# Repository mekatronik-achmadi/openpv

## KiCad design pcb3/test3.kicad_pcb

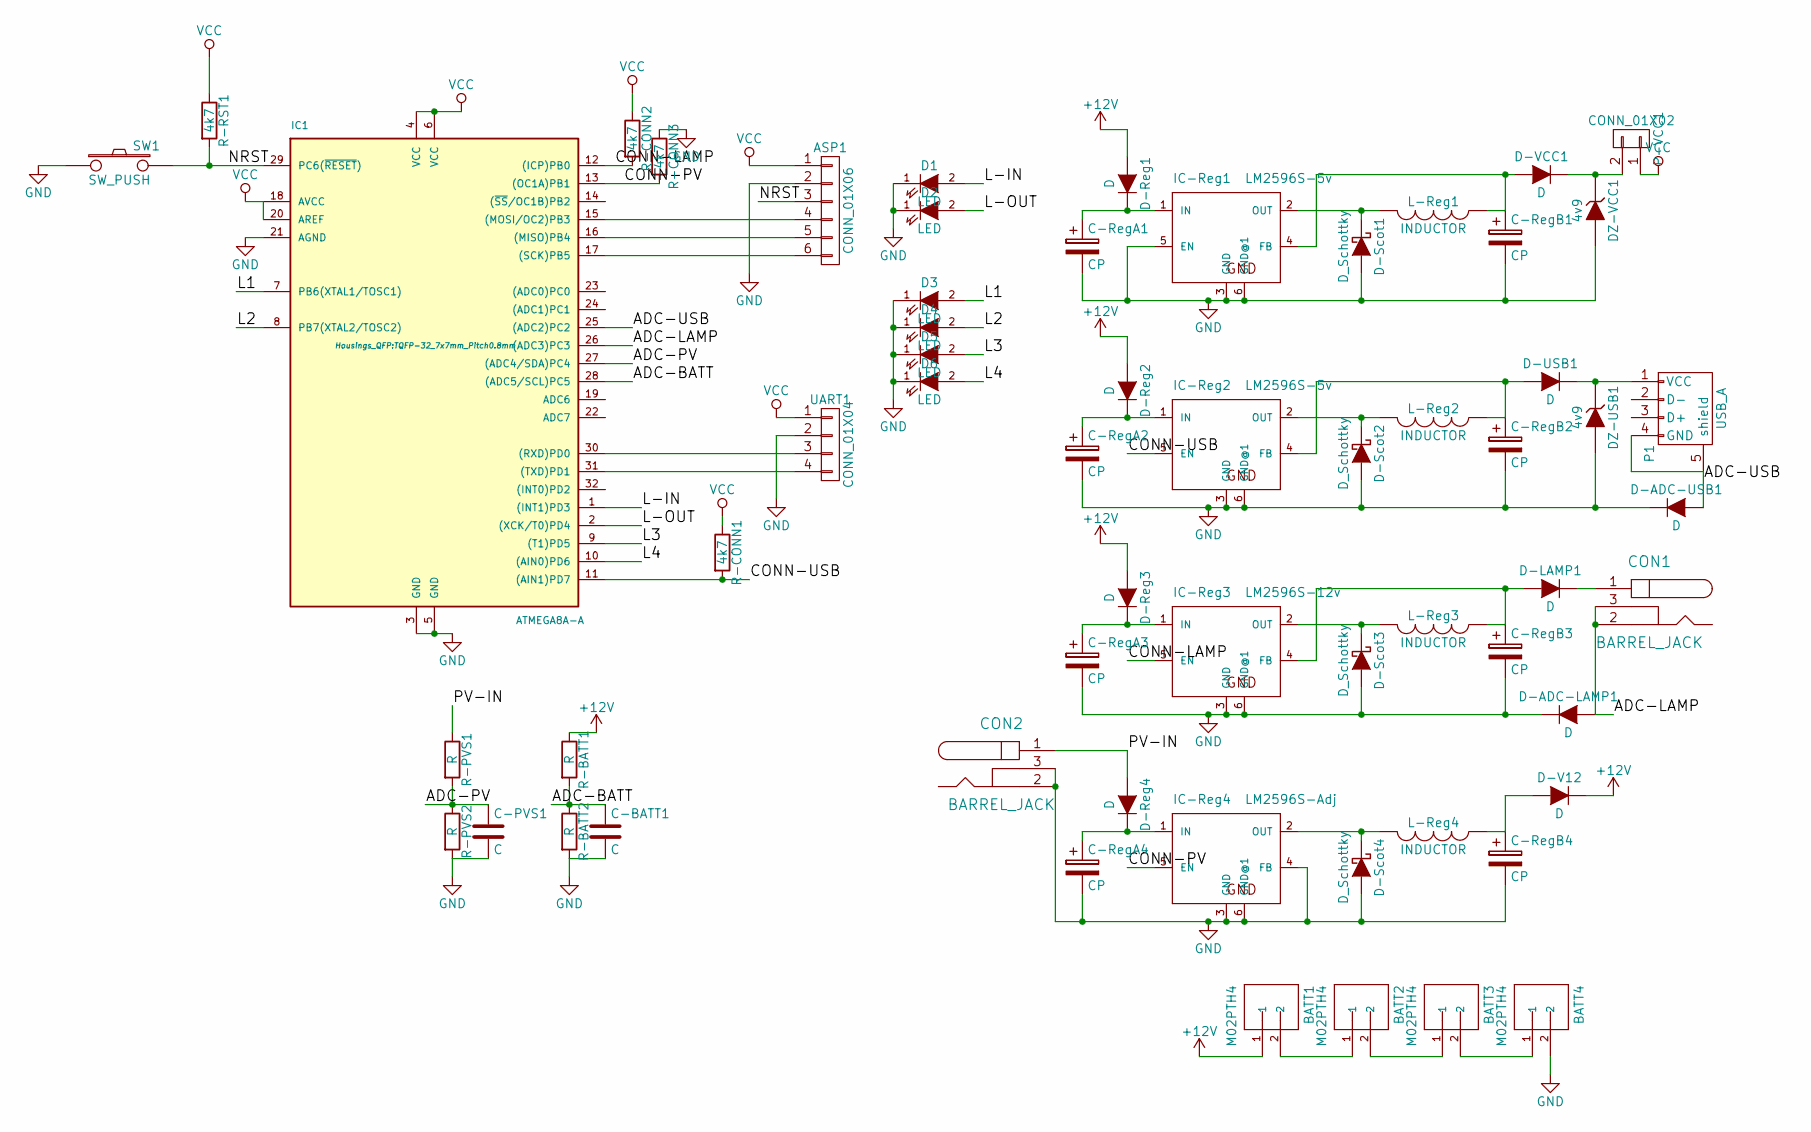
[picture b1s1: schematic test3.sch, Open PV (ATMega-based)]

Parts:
ASP1: CONN_01X06; Pin_Header_Straight_1x06
BATT1, BATT2, BATT3, BATT4: M02PTH4; SparkFun-1X02_XTRA_BIG
C-BATT1: C; C_Rect_L7_W2_P5
C-PVS1: C; C_Rect_L7_W2_P5
C-RegA1, C-RegA2, C-RegA3, C-RegA4: CP; C_Radial_D5_L6_P2.5
C-RegB1, C-RegB2, C-RegB3, C-RegB4: CP; C_Radial_D5_L6_P2.5
CON1, CON2: BARREL_JACK; JACK_ALIM
D1, D2, D3, D4, D5, D6: LED; LED-3MM
D-ADC-LAMP1: D; Diode_DO-35_SOD27_Horizontal_RM10
D-ADC-USB1: D; Diode_DO-35_SOD27_Horizontal_RM10
D-LAMP1: D; Diode_DO-35_SOD27_Horizontal_RM10
D-Reg1, D-Reg2, D-Reg3, D-Reg4: D; Diode_DO-35_SOD27_Horizontal_RM10
D-Scot1, D-Scot2, D-Scot3, D-Scot4: D_Schottky; Diode_DO-35_SOD27_Horizontal_RM10
D-USB1: D; Diode_DO-35_SOD27_Horizontal_RM10
D-V12: D; Diode_DO-35_SOD27_Horizontal_RM10
D-VCC1: D; Diode_DO-35_SOD27_Horizontal_RM10
DZ-USB1: 4v9; Diode_DO-35_SOD27_Horizontal_RM10
DZ-VCC1: 4v9; Diode_DO-35_SOD27_Horizontal_RM10
IC1: ATMEGA8A-A; TQFP-32_7x7mm_Pitch0.8mm
IC-Reg1, IC-Reg2: LM2596S-5v; TO-263-5Lead
IC-Reg3: LM2596S-12v; TO-263-5Lead
IC-Reg4: LM2596S-Adj; TO-263-5Lead
L-Reg1, L-Reg2, L-Reg3, L-Reg4: INDUCTOR; INDUCTOR_V
P1: USB_A
P-VCC1: CONN_01X02; Pin_Header_Straight_1x02
R-BATT1, R-BATT2: R; Resistor_Horizontal_RM10mm
R-CONN1, R-CONN2, R-CONN3: 4k7; Resistor_Horizontal_RM10mm
R-PVS1, R-PVS2: R; Resistor_Horizontal_RM10mm
R-RST1: 4k7; Resistor_Horizontal_RM10mm
SW1: SW_PUSH; switch-omron-B3F-10XX
UART1: CONN_01X04; Pin_Header_Straight_1x04

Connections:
+12V: BATT1.1, D-Reg1.2 (A), D-Reg2.2 (A), D-Reg3.2 (A), D-V12.1 (K), R-BATT1.1
/ADC-BATT: C-BATT1.1, IC1.28 ((ADC5/SCL)PC5), R-BATT1.2, R-BATT2.1
/ADC-LAMP: CON1.2, CON1.3, D-ADC-LAMP1.2 (A), IC1.26 ((ADC3)PC3)
/ADC-PV: C-PVS1.1, IC1.27 ((ADC4/SDA)PC4), R-PVS1.2, R-PVS2.1
/ADC-USB: D-ADC-USB1.2 (A), IC1.25 ((ADC2)PC2), P1.4 (GND), P1.5 (shield)
/CONN-LAMP: IC1.12 ((ICP)PB0), IC-Reg3.5 (EN), R-CONN2.2
/CONN-PV: IC1.13 ((OC1A)PB1), IC-Reg4.5 (EN), R-CONN3.2
/CONN-USB: IC1.11 ((AIN1)PD7), IC-Reg2.5 (EN), R-CONN1.2
/L1: D3.2 (A), IC1.7 (PB6(XTAL1/TOSC1))
/L2: D4.2 (A), IC1.8 (PB7(XTAL2/TOSC2))
/L3: D5.2 (A), IC1.9 ((T1)PD5)
/L4: D6.2 (A), IC1.10 ((AIN0)PD6)
/L-IN: D1.2 (A), IC1.1 ((INT1)PD3)
/L-OUT: D2.2 (A), IC1.2 ((XCK/T0)PD4)
/NRST: ASP1.3, IC1.29 (PC6(~RESET~)), R-RST1.2, SW1.2
/PV-IN: CON2.1, D-Reg4.2 (A), R-PVS1.1
GND: ASP1.2, BATT4.2, C-BATT1.2, C-PVS1.2, C-RegA1.2, C-RegA2.2, C-RegA3.2, C-RegA4.2, C-RegB1.2, C-RegB2.2, C-RegB3.2, C-RegB4.2, CON2.2, CON2.3, D1.1 (K), D2.1 (K), D3.1 (K), D4.1 (K), D5.1 (K), D6.1 (K), D-ADC-LAMP1.1 (K), D-ADC-USB1.1 (K), D-Scot1.2 (A), D-Scot2.2 (A), D-Scot3.2 (A), D-Scot4.2 (A), DZ-USB1.2 (A), DZ-VCC1.2 (A), IC1.3 (GND), IC1.5 (GND), IC1.21 (AGND), IC-Reg1.3 (GND), IC-Reg1.5 (EN), IC-Reg1.6 (GND@1), IC-Reg2.3 (GND), IC-Reg2.6 (GND@1), IC-Reg3.3 (GND), IC-Reg3.6 (GND@1), IC-Reg4.3 (GND), IC-Reg4.4 (FB), IC-Reg4.6 (GND@1), R-BATT2.2, R-CONN3.1, R-PVS2.2, SW1.1, UART1.2
unnamed: ASP1.4, IC1.15 ((MOSI/OC2)PB3)
unnamed: ASP1.5, IC1.16 ((MISO)PB4)
unnamed: ASP1.6, IC1.17 ((SCK)PB5)
unnamed: BATT1.2, BATT2.1
unnamed: BATT2.2, BATT3.1
unnamed: BATT3.2, BATT4.1
unnamed: C-RegA1.1, D-Reg1.1 (K), IC-Reg1.1 (IN)
unnamed: C-RegA2.1, D-Reg2.1 (K), IC-Reg2.1 (IN)
unnamed: C-RegA3.1, D-Reg3.1 (K), IC-Reg3.1 (IN)
unnamed: C-RegA4.1, D-Reg4.1 (K), IC-Reg4.1 (IN)
unnamed: C-RegB1.1, D-VCC1.2 (A), IC-Reg1.4 (FB), L-Reg1.1
unnamed: C-RegB2.1, D-USB1.2 (A), IC-Reg2.4 (FB), L-Reg2.1
unnamed: C-RegB3.1, D-LAMP1.2 (A), IC-Reg3.4 (FB), L-Reg3.1
unnamed: C-RegB4.1, D-V12.2 (A), L-Reg4.1
unnamed: CON1.1, D-LAMP1.1 (K)
unnamed: D-Scot1.1 (K), IC-Reg1.2 (OUT), L-Reg1.2
unnamed: D-Scot2.1 (K), IC-Reg2.2 (OUT), L-Reg2.2
unnamed: D-Scot3.1 (K), IC-Reg3.2 (OUT), L-Reg3.2
unnamed: D-Scot4.1 (K), IC-Reg4.2 (OUT), L-Reg4.2
unnamed: D-USB1.1 (K), DZ-USB1.1 (K), P1.1 (VCC)
unnamed: D-VCC1.1 (K), DZ-VCC1.1 (K), P-VCC1.2
unnamed: IC1.30 ((RXD)PD0), UART1.3
unnamed: IC1.31 ((TXD)PD1), UART1.4
VCC: ASP1.1, IC1.4 (VCC), IC1.6 (VCC), IC1.18 (AVCC), IC1.20 (AREF), P-VCC1.1, R-CONN1.1, R-CONN2.1, R-RST1.1, UART1.1

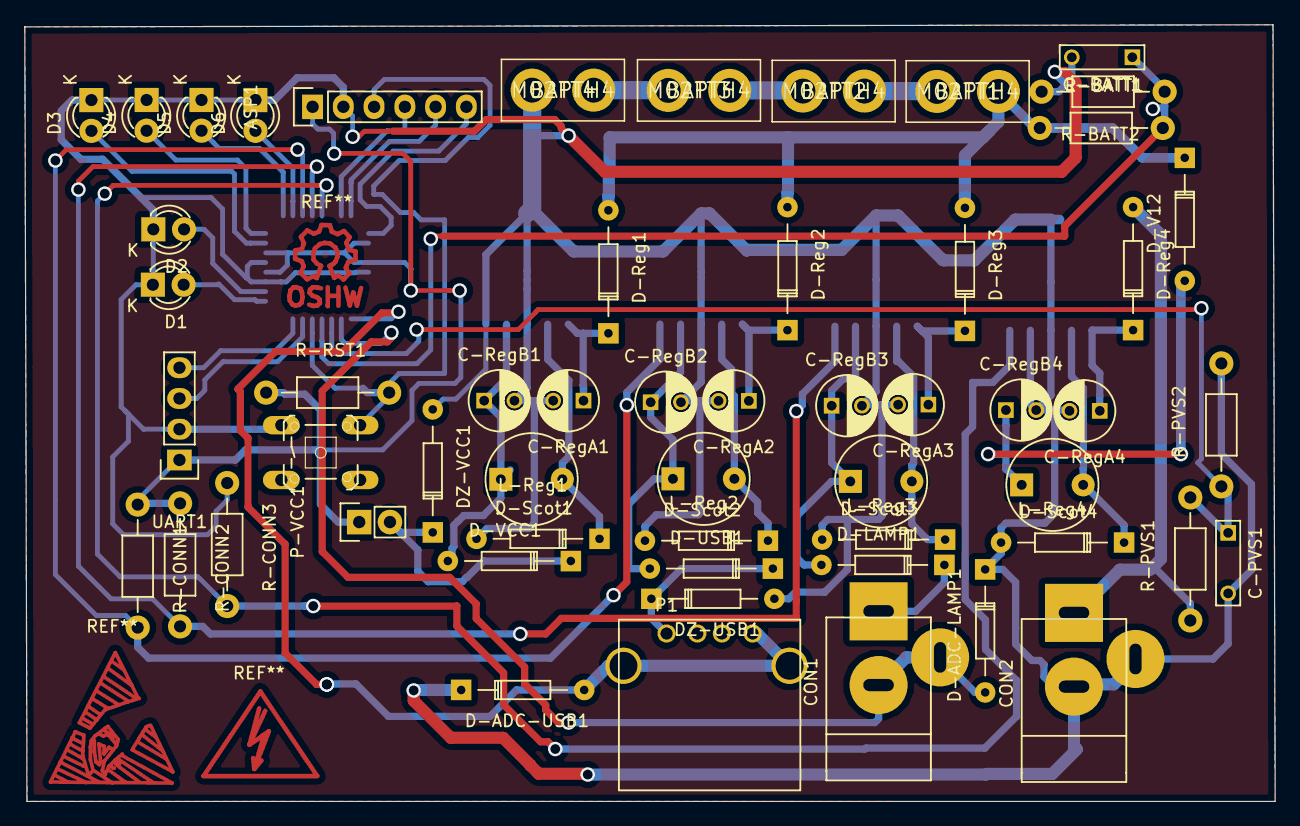
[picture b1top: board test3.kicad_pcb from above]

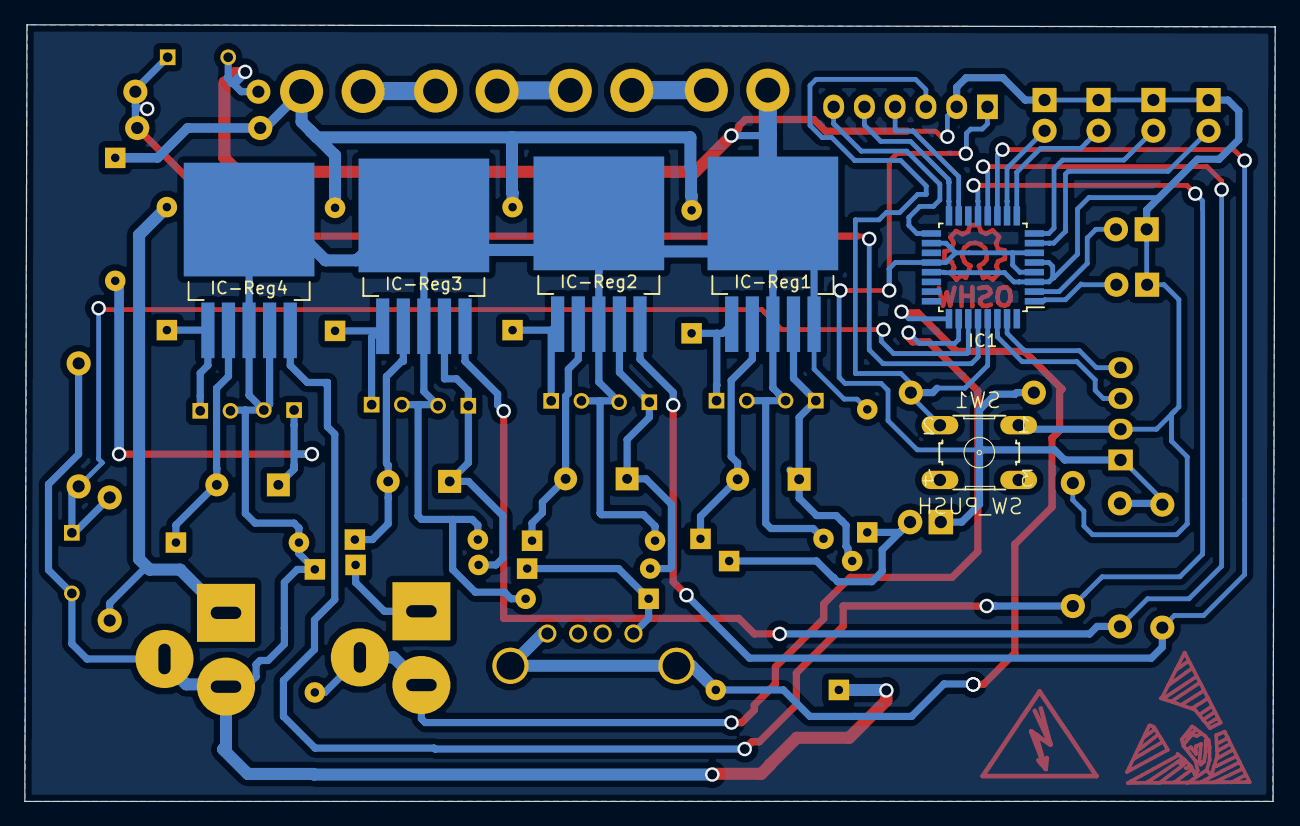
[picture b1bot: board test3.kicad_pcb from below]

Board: 2 copper layers, 103.3 x 64.1 mm, 60 parts (5 on the bottom side), 41 nets.

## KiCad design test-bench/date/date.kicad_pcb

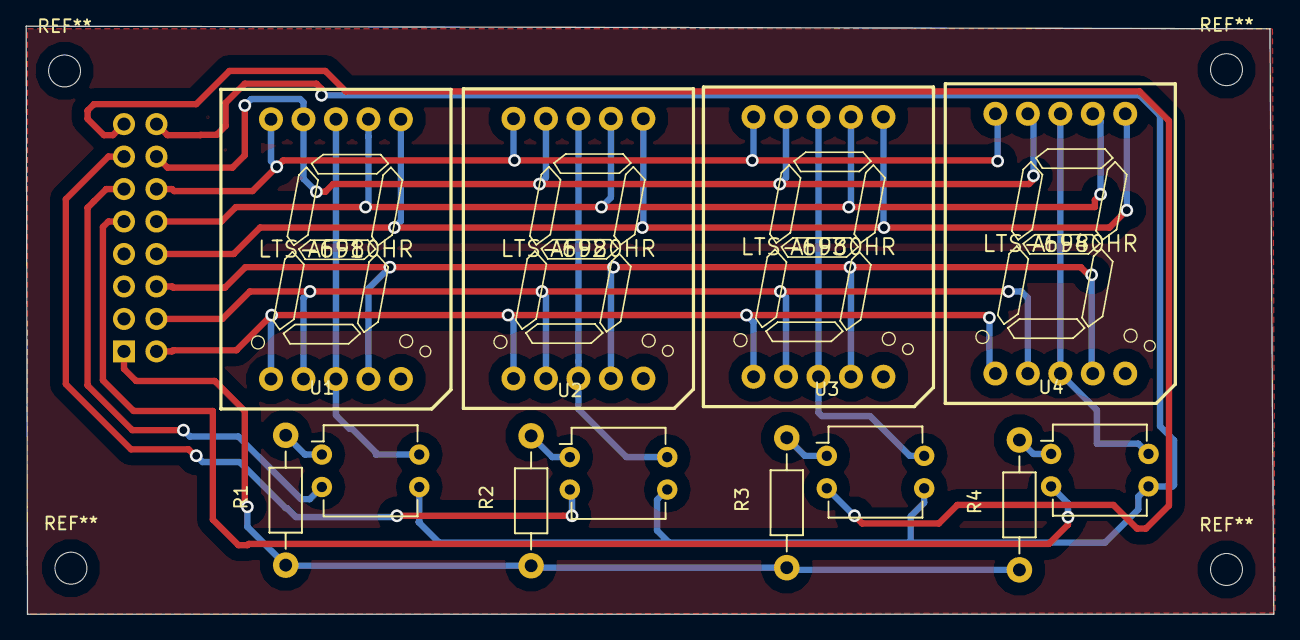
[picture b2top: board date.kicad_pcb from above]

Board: 2 copper layers, 97.6 x 46.0 mm, 13 parts (1 on the bottom side), 21 nets.

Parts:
AFF1, AFF2, AFF3, AFF4: LTS-6980HR; SparkFun-7-SEGMENT-1%22PTH
P1: CONN_02X08; Pin_Header_Straight_2x08
R1, R2, R3, R4: 330; Resistor_Horizontal_RM10mm
U1, U2, U3, U4: PC817; DIP-4_W7.62mm

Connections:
/DA: P1.15, U3.2
/DB: P1.13, U2.2
/DC: P1.11, U1.2
/DD: P1.9, U4.2
/LA: AFF1.7, AFF2.7, AFF3.7, AFF4.7, P1.10
/LB: AFF1.6, AFF2.6, AFF3.6, AFF4.6, P1.8
/LC: AFF1.4, AFF2.4, AFF3.4, AFF4.4, P1.6
/LD: AFF1.2, AFF2.2, AFF3.2, AFF4.2, P1.4
/LE: AFF1.1, AFF2.1, AFF3.1, AFF4.1, P1.2
/LF: AFF1.9, AFF2.9, AFF3.9, AFF4.9, P1.14
/LG: AFF1.10, AFF2.10, AFF3.10, AFF4.10, P1.12
GND: P1.16, U1.3, U2.3, U3.3, U4.3
unnamed: AFF1.3, AFF1.8, U1.4
unnamed: AFF2.3, AFF2.8, U2.4
unnamed: AFF3.3, AFF3.8, U3.4
unnamed: AFF4.3, AFF4.8, U4.4
unnamed: R1.2, U1.1
unnamed: R2.2, U2.1
unnamed: R3.2, U3.1
unnamed: R4.2, U4.1
VCC: P1.1, R1.1, R2.1, R3.1, R4.1
